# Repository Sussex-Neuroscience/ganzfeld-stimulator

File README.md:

# ganzfeld-stimulator

## Overview
We built a 'full-field' LED stimulator as a visual stimulus generator for in vivo rodent physiology experiments. The stimulator can generate arbitrary temporal patterns of green and UV light (chromatic channels the mouse visual system is sensitive to) such as high frequency flicker or sinusoidal dimming. Stimulation patterns are generated using PWM signals from a microcontroller.

## Parts 

| Item | Link | Quantity | Cost | Datasheet |
|------|------|----------|------|-----------|
| **LEDS**| | | |
| UV LED   |[C3535U- UNL1-A1G11H-380 TSLC, UV LED, 390nm 480mW 125 °, 2-Pin Surface Mount package](https://uk.rs-online.com/web/p/uv-leds/9033769) | (6 x 6 array) = 36 + any spares | £6.88 each | [From RS](https://uk.rs-online.com/web/p/uv-leds/9033769)|
| Green LED | [ams OSRAM3 V Green LED PLCC 2 SMD, TOPLED LT T673-Q1R2-25](https://uk.rs-online.com/web/p/leds/6648197) | (6 x 6 array) = 36 + any spares | £0.196 each| [From RS](https://uk.rs-online.com/web/p/leds/6648197) |
| LED mounting PCB |  [Custom PCB board for mounting LEDs](repo link) | 6 (Each board is populated with 6 of green and 6 UV) | ?? | 
| Soldering stencil | [Custom stencil](repo link) | 1 | ?? |
|**PSU and Drivers**|||
| LED Driver | [Recom LED Driver, 2 → 35V dc Output, 350mA Output, Constant Current Dimmable](https://uk.rs-online.com/web/p/led-drivers/0416913) | ?? | £12.16 each | [detailed](https://g.recomcdn.com/media/Datasheet/pdf/.fYUQjOlW/.t2a80a771bdbb0ef300f7/Datasheet-93/RCD-24.pdf) |
| PSU | [12V dc Output, 5A Output](https://uk.rs-online.com/web/p/ac-dc-adapters/8808408?gb=s) | ?? | £21.38 each |
|**Box Construction**| | |
| Structure | [MakerBeam starter kit](https://www.technobotsonline.com/makerbeamxl-regular-starter-kit-in-black-anodised-threaded.html) | 1 | £102.95 (possible to buy specific parts separately) | [200mm beam technical drawing](https://drive.google.com/drive/folders/0B8h5C_ek_fmKa2E4a2I1NEtXWTQ?resourcekey=0-tFenALGdWDfK6WEzQJMuUQ), [50mm beam technical drawing](https://drive.google.com/drive/folders/1401xnkoKaVmki9BlENUgdnQiJKWathsU) |
| Structure | [MakerBeam Construction Cubes](https://www.technobotsonline.com/makerbeam-xl-black-corner-cubes-pack-of-12.html) | 1x box of 12 (need 8) |  £18.00 for 12 | [corner cube technical drawing](https://drive.google.com/drive/folders/0B8h5C_ek_fmKcEFvbkl0NWtaZ28?resourcekey=0-kpjmWWiNEXZBVXVSDK05Yg) |
| Reflective Walls + floor | [RS PRO Aluminium Metal Sheet 300mm x 500mm, 2mm Thick](https://uk.rs-online.com/web/p/metal-sheets/0434059) | 1*(200x200mm), 4*(50x200mm) | £49.07 for 5 300x500mm sheets |
|**Diffuser** | | |
| Tracing paper | e.g. [amazon](https://www.amazon.co.uk/GLADFRESIT-Translucent-Architecture-Scrapbooking-Printing/dp/B0C3VX6JPX/ref=asc_df_B0C3VX6JPX/?tag=googshopuk-21&linkCode=df0&hvadid=662823090693&hvpos=&hvnetw=g&hvrand=10142952570193465802&hvpone=&hvptwo=&hvqmt=&hvdev=c&hvdvcmdl=&hvlocint=&hvlocphy=1006565&hvtargid=pla-2196737734548&psc=1&mcid=5f2980b322dd33169770b0c6ecff1379) | 2 sheets + spares | £5.99 |
| Diffusion holder | [Custom 3D printed part](repo link) | ?? | ?? |

## Construction

### Building the stimulator structure
We opted to make a 200x200mm box with a ~50mm depth for achieving a uniform intensity of light. The box can easily be scaled larger and smaller to suit your purposes accordingly.

1) Join 4 x 200mm beams to form a square, using the construction cubes in the corners. You need to make 2 of these for the top and bottom of the box.
2) Cut a ~200x200mm piece of aluminium to slot into the centre of one of the square. You'll need to slightly adjust the size so it fits into the grooves of the beams. This will provide the base for the LED PCBs. (drill a hole of diameter xx for wires)
3) Add 4 x 50mm beams upright to the 4 corners of one of the squares.
4) Screw in the other 200x200mm square to these upright beams to form the top of the box.
5) Cut 4 more pieces of aluminium to form the 4 walls of the box. You want them to be flush with the top of the box to maximise reflectivity of the light inside the box.

### Populating the LEDs on the PCB boards
Use the soldering stencil to populate each of the PCB boards with 6 x green and 6 x UV LEDs. The LEDs are arranged in alternating rows of 3 green/UV.

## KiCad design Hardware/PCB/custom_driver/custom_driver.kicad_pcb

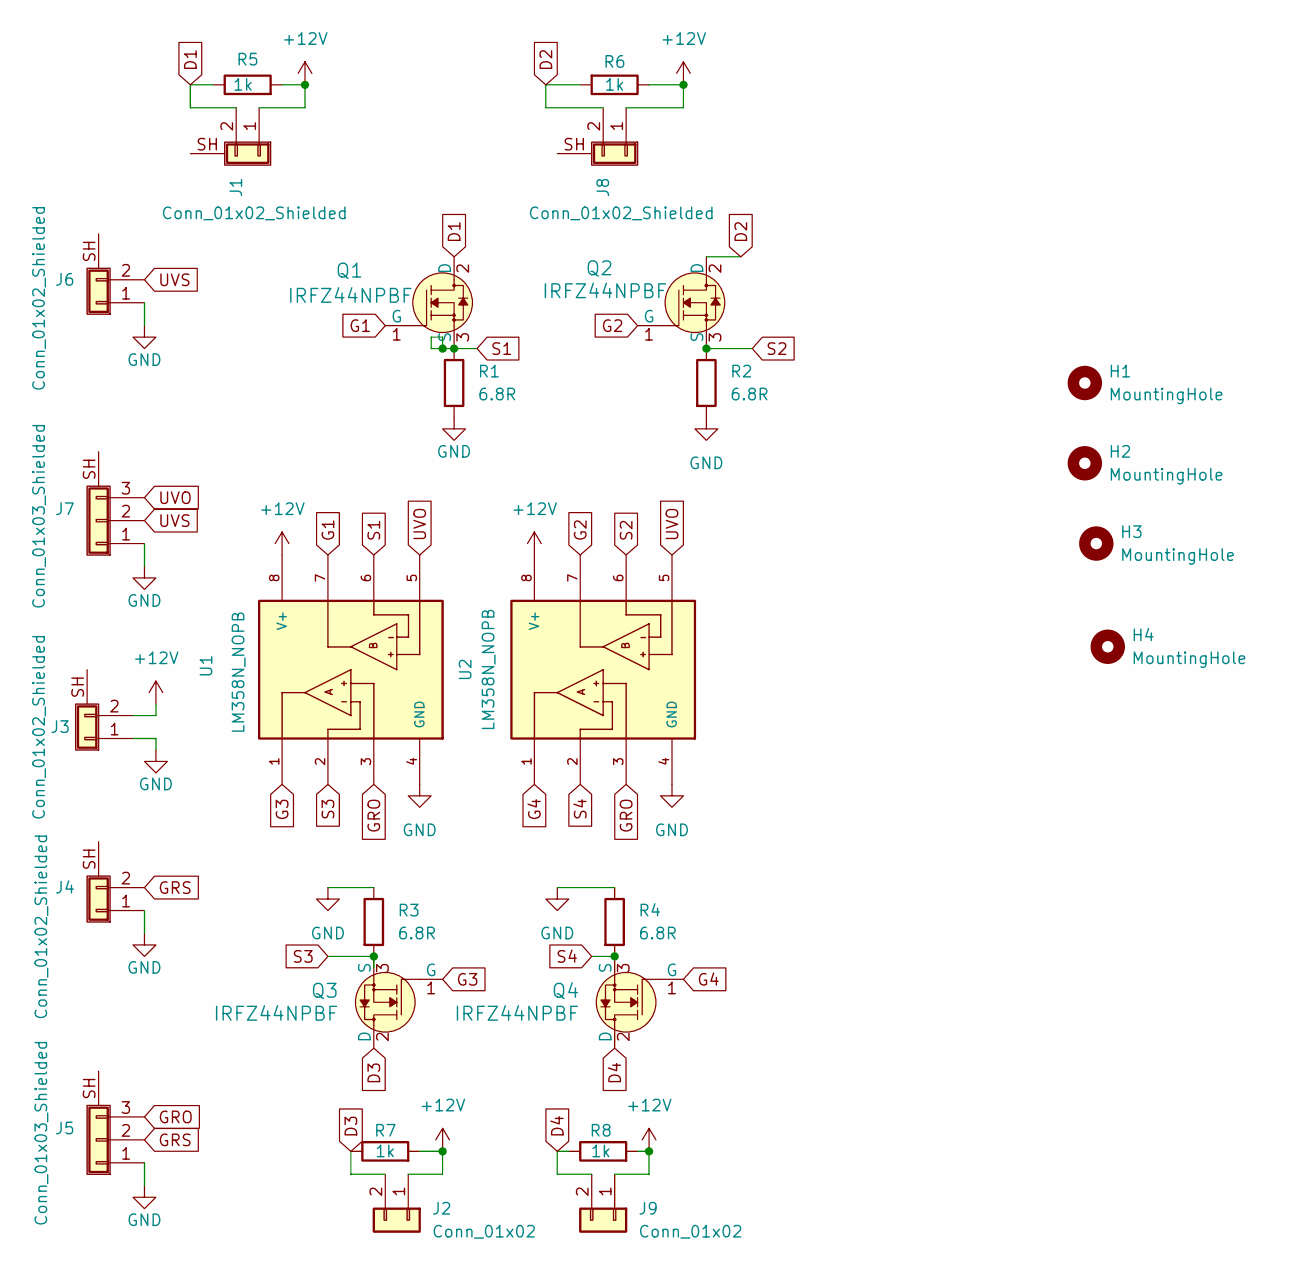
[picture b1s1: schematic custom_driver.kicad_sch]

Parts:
H1, H2, H3, H4: MountingHole; MountingHole_3.2mm_M3
J1, J3, J4, J6, J8: Conn_01x02_Shielded; PinSocket_1x02_P2.54mm_Horizontal
J2, J9: Conn_01x02; PinSocket_1x02_P2.54mm_Horizontal
J5, J7: Conn_01x03_Shielded; PinSocket_1x03_P2.54mm_Horizontal
Q1, Q2, Q3, Q4: IRFZ44NPBF; TO-220-3; MPN IRF510PBF; Digi-Key_PN IRF510PBF-ND
R1, R2: 6.8R; R_Axial_Power_L38.0mm_W6.4mm_P40.64mm
R3, R4: 6.8R; R_Axial_DIN0207_L6.3mm_D2.5mm_P7.62mm_Horizontal
R5, R6, R7, R8: 1k; R_Axial_DIN0207_L6.3mm_D2.5mm_P7.62mm_Horizontal
U1, U2: LM358N_NOPB; LM358N_NOP

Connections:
+12V: J1.1, J2.1, J3.2, J8.1, J9.1, R5.2, R6.1, R7.2, R8.2, U1.8 (V+), U2.8 (V+)
D1: J1.2, Q1.2 (D), R5.1
D2: J8.2, Q2.2 (D), R6.2
D3: J2.2, Q3.2 (D), R7.1
D4: J9.2, Q4.2 (D), R8.1
G1: Q1.1 (G), U1.7
G2: Q2.1 (G), U2.7
G3: Q3.1 (G), U1.1
G4: Q4.1 (G), U2.1
GND: J3.1, J4.1, J5.1, J6.1, J7.1, R1.2, R2.2, R3.1, R4.1, U1.4 (GND), U2.4 (GND)
GRO: J5.3, U1.3, U2.3
GRS: J4.2, J5.2
S1: Q1.3 (S), R1.1, U1.6
S2: Q2.3 (S), R2.1, U2.6
S3: Q3.3 (S), R3.2, U1.2
S4: Q4.3 (S), R4.2, U2.2
UVO: J7.3, U1.5, U2.5
UVS: J6.2, J7.2

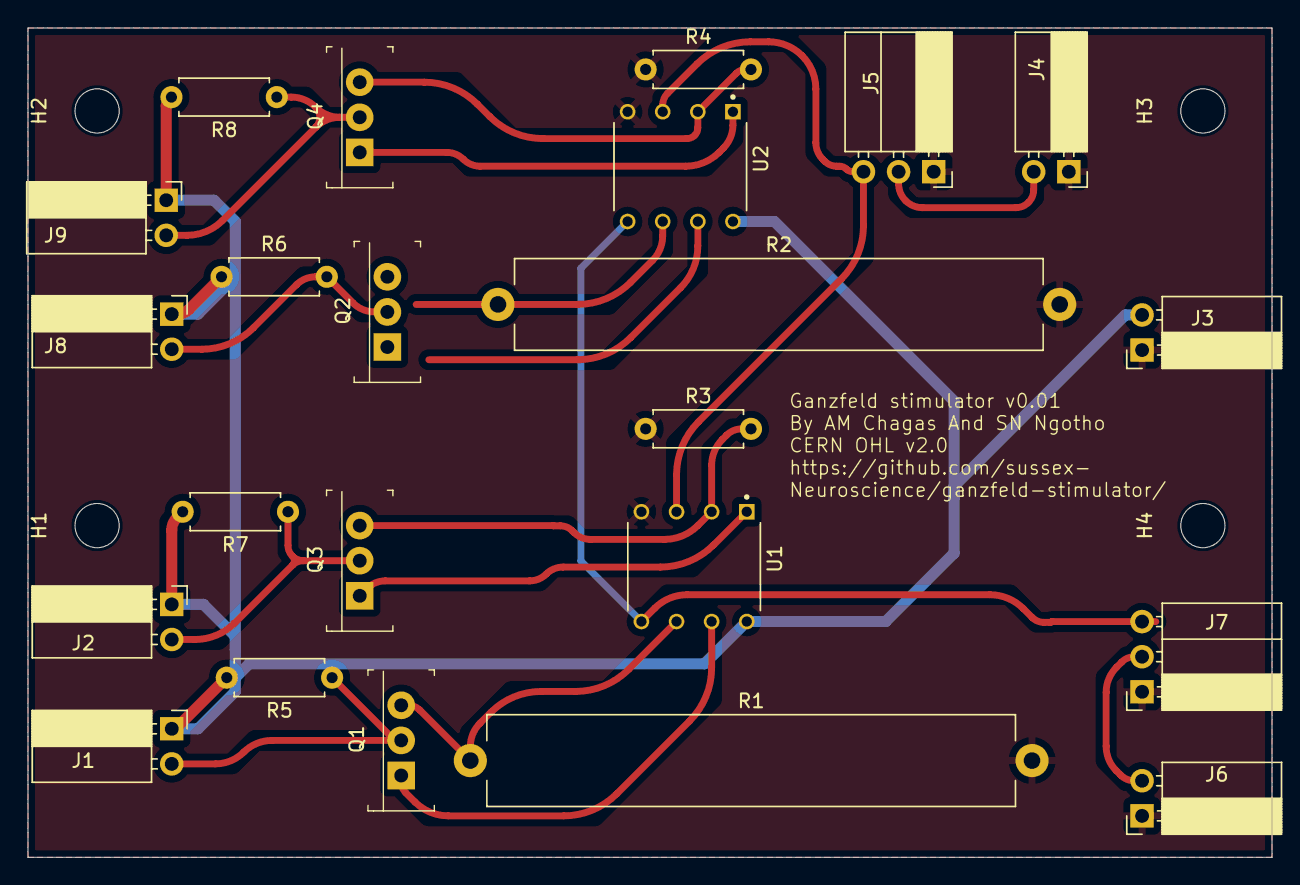
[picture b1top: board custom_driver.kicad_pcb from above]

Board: 2 copper layers, 90.0 x 60.0 mm, 27 parts (0 on the bottom side), 18 nets.

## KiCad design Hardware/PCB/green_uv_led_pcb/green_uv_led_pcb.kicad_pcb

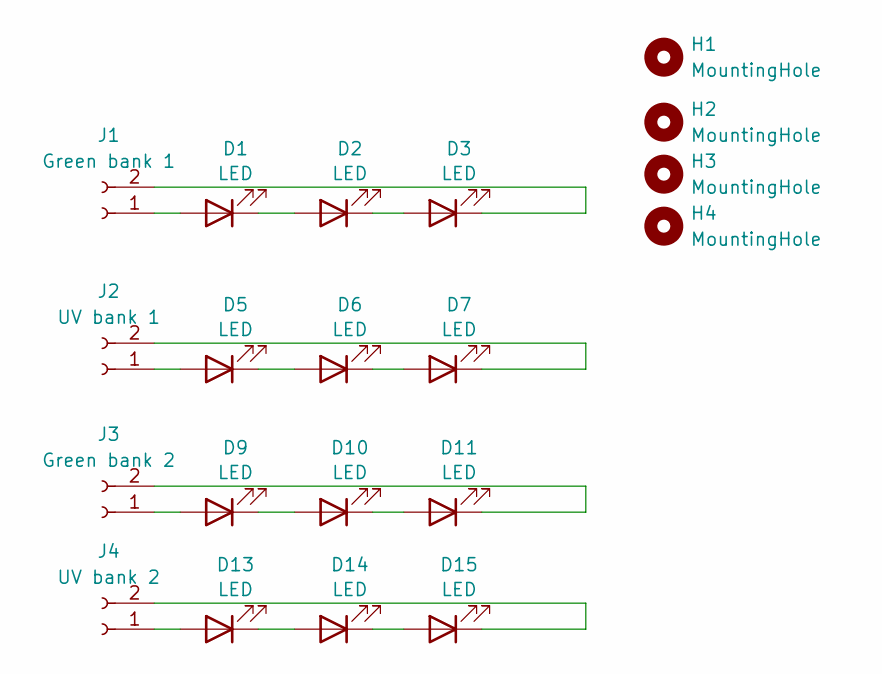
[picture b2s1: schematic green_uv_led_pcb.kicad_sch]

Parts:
D1, D2, D3, D9, D10, D11: LED; LED_PLCC-2_3.4x3.0mm_KA
D5, D6, D7, D13, D14, D15: LED; LED_Cree-XP
H1, H2, H3, H4: MountingHole; MountingHole_3.2mm_M3
J1: Green bank 1; PinSocket_1x02_P2.54mm_Horizontal
J2: UV bank 1; PinSocket_1x02_P2.54mm_Horizontal
J3: Green bank 2; PinSocket_1x02_P2.54mm_Horizontal
J4: UV bank 2; PinSocket_1x02_P2.54mm_Horizontal

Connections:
unnamed: D1.2 (A), J1.1
unnamed: D1.1 (K), D2.2 (A)
unnamed: D2.1 (K), D3.2 (A)
unnamed: D3.1 (K), J1.2
unnamed: D5.2 (A), J2.1
unnamed: D5.1 (K), D6.2 (A)
unnamed: D6.1 (K), D7.2 (A)
unnamed: D7.1 (K), J2.2
unnamed: D9.2 (A), J3.1
unnamed: D9.1 (K), D10.2 (A)
unnamed: D10.1 (K), D11.2 (A)
unnamed: D11.1 (K), J3.2
unnamed: D13.2 (A), J4.1
unnamed: D13.1 (K), D14.2 (A)
unnamed: D14.1 (K), D15.2 (A)
unnamed: D15.1 (K), J4.2

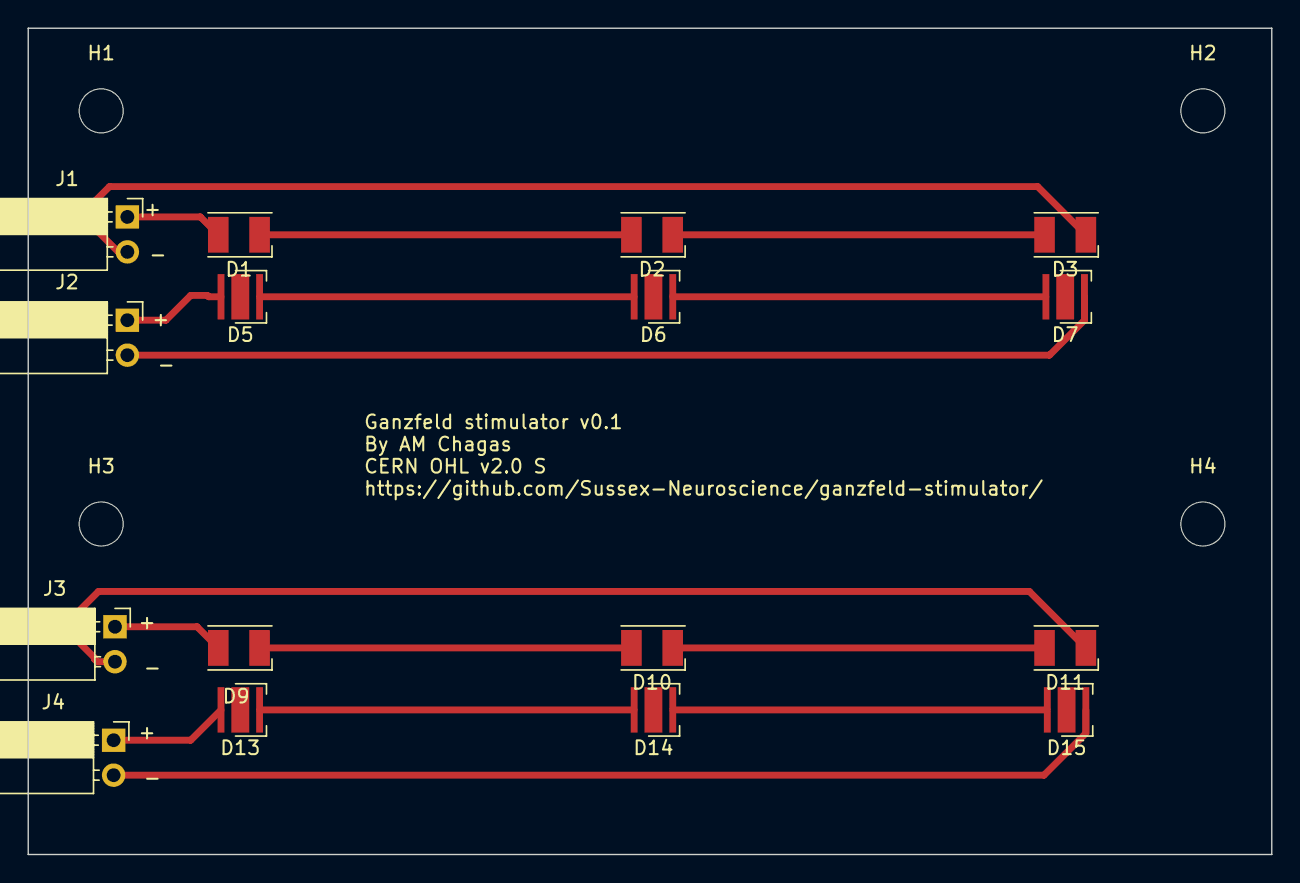
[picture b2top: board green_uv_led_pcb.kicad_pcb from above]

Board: 2 copper layers, 90.3 x 60.0 mm, 20 parts (0 on the bottom side), 16 nets.

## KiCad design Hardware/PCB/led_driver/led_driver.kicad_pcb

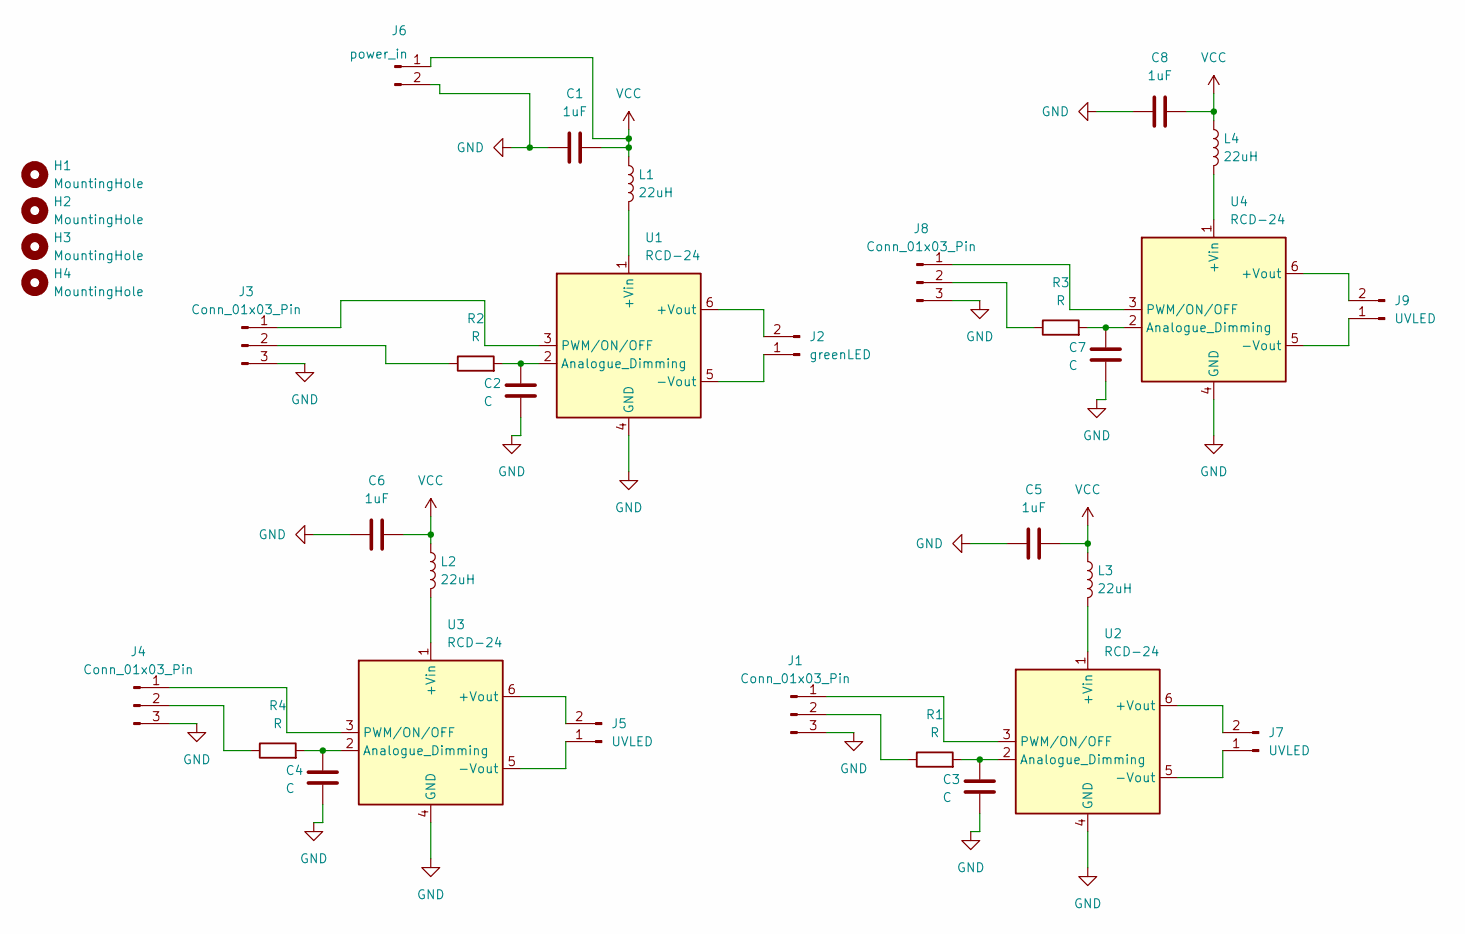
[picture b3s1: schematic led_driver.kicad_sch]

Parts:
C1, C5, C6, C8: 1uF; CP_Radial_Tantal_D4.5mm_P2.50mm
C2, C3, C4, C7: C; CP_Radial_Tantal_D4.5mm_P2.50mm
H1, H2, H3, H4: MountingHole; MountingHole_3.2mm_M3
J1, J3, J4, J8: Conn_01x03_Pin; JST_XH_B3B-XH-A_1x03_P2.50mm_Vertical
J2: greenLED; JST_XH_B2B-XH-A_1x02_P2.50mm_Vertical
J5, J7, J9: UVLED; JST_XH_B2B-XH-A_1x02_P2.50mm_Vertical
J6: power_in; JST_XH_B2B-XH-A_1x02_P2.50mm_Vertical
L1, L2, L3, L4: 22uH; L_Radial_D6.0mm_P4.00mm
R1, R2, R3, R4: R; R_Axial_DIN0411_L9.9mm_D3.6mm_P12.70mm_Horizontal
U1, U2, U3, U4: RCD-24; Converter_DCDC_RECOM_RCD-24_THT

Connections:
GND: C1.1, C2.2, C3.2, C4.2, C5.1, C6.1, C7.2, C8.1, J1.3, J3.3, J4.3, J6.2, J8.3, U1.4 (GND), U2.4 (GND), U3.4 (GND), U4.4 (GND)
unnamed: J1.1, U2.3 (PWM/ON/OFF)
unnamed: J1.2, R1.1
unnamed: J2.1, U1.5 (-Vout)
unnamed: J2.2, U1.6 (+Vout)
unnamed: J3.1, U1.3 (PWM/ON/OFF)
unnamed: J3.2, R2.1
unnamed: J4.1, U3.3 (PWM/ON/OFF)
unnamed: J4.2, R4.1
unnamed: J5.1, U3.5 (-Vout)
unnamed: J5.2, U3.6 (+Vout)
unnamed: J7.1, U2.5 (-Vout)
unnamed: J7.2, U2.6 (+Vout)
unnamed: J8.1, U4.3 (PWM/ON/OFF)
unnamed: J8.2, R3.1
unnamed: J9.1, U4.5 (-Vout)
unnamed: J9.2, U4.6 (+Vout)
unnamed: L1.2, U1.1 (+Vin)
unnamed: C2.1, R2.2, U1.2 (Analogue_Dimming)
unnamed: L3.2, U2.1 (+Vin)
unnamed: C3.1, R1.2, U2.2 (Analogue_Dimming)
unnamed: L2.2, U3.1 (+Vin)
unnamed: C4.1, R4.2, U3.2 (Analogue_Dimming)
unnamed: L4.2, U4.1 (+Vin)
unnamed: C7.1, R3.2, U4.2 (Analogue_Dimming)
VCC: C1.2, C5.2, C6.2, C8.2, J6.1, L1.1, L2.1, L3.1, L4.1

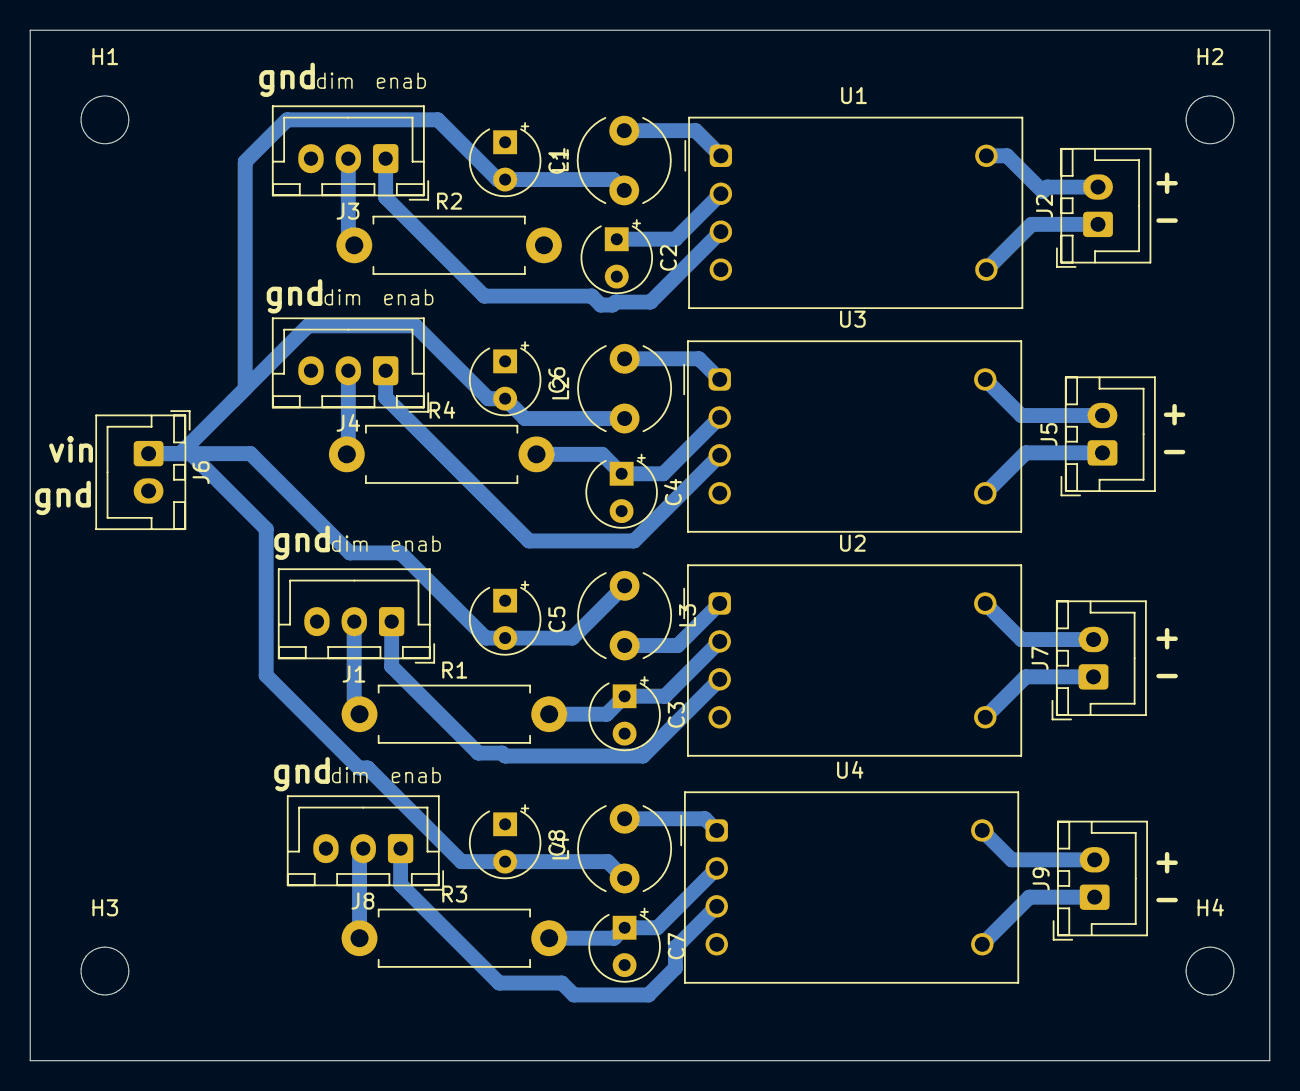
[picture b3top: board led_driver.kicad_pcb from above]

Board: 2 copper layers, 83.0 x 69.0 mm, 33 parts (0 on the bottom side), 26 nets.

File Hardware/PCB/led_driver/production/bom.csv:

Designator,Footprint,Quantity,Value,LCSC Part #
"C1, C5, C6, C8",CP_Radial_Tantal_D4.5mm_P2.50mm,4,1uF,
"C2, C3, C4, C7",CP_Radial_Tantal_D4.5mm_P2.50mm,4,C,
"J1, J3, J4, J8",JST_XH_B3B-XH-A_1x03_P2.50mm_Vertical,4,Conn_01x03_Pin,
J2,JST_XH_B2B-XH-A_1x02_P2.50mm_Vertical,1,greenLED,
"J5, J7, J9",JST_XH_B2B-XH-A_1x02_P2.50mm_Vertical,3,UVLED,
J6,JST_XH_B2B-XH-A_1x02_P2.50mm_Vertical,1,power_in,
"L1, L2, L3, L4",L_Radial_D6.0mm_P4.00mm,4,22uH,
"R1, R2, R3, R4",R_Axial_DIN0411_L9.9mm_D3.6mm_P12.70mm_Horizontal,4,R,
"U1, U2, U3, U4",Converter_DCDC_RECOM_RCD-24_THT,4,RCD-24,

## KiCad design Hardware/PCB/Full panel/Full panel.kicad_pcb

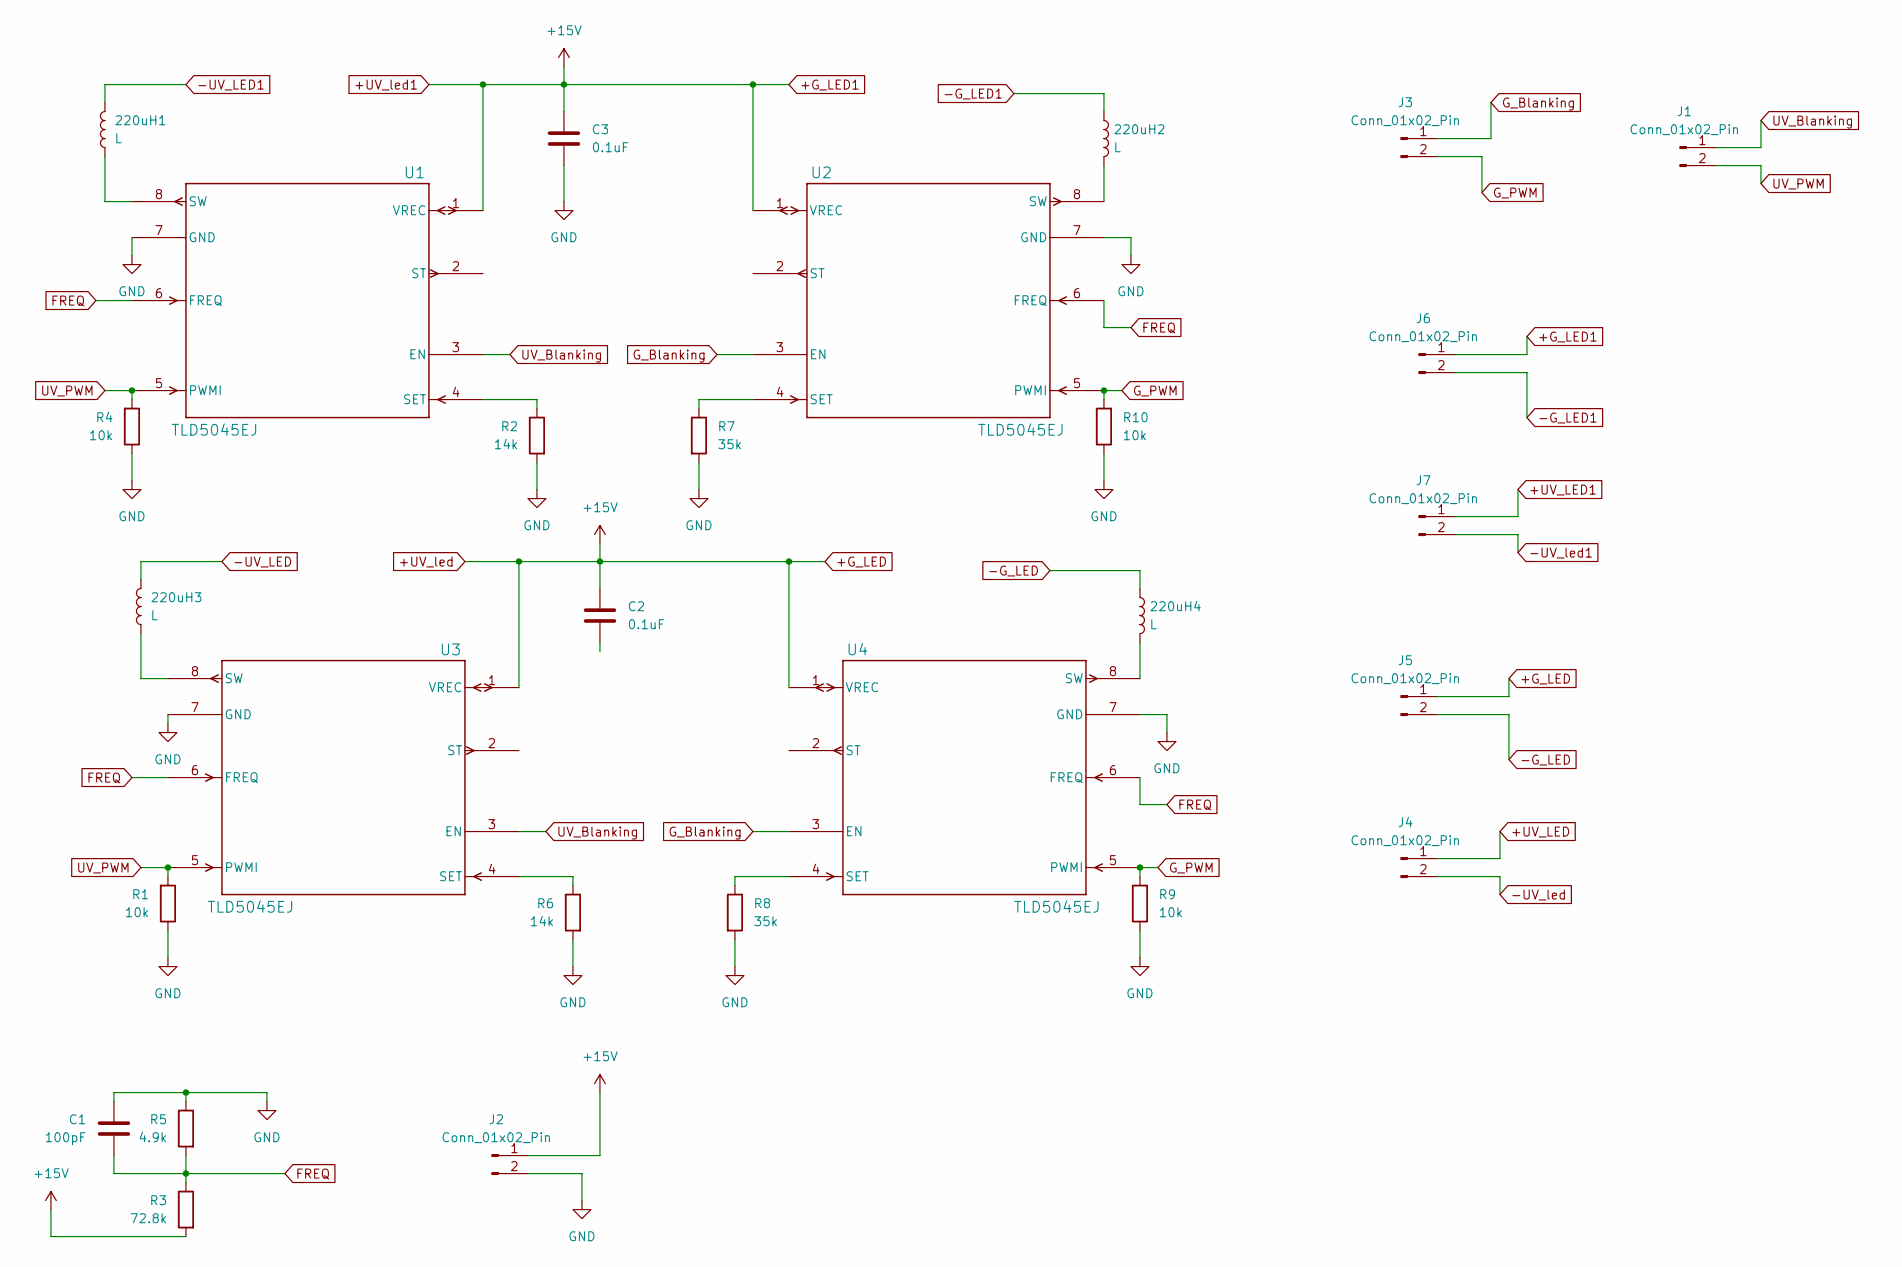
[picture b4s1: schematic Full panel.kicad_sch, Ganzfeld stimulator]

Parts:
220uH1, 220uH2, 220uH3, 220uH4: L; C_0805_2012Metric_Pad1.18x1.45mm_HandSolder
C1: 100pF; C_0805_2012Metric_Pad1.18x1.45mm_HandSolder
C2, C3: 0.1uF; C_0805_2012Metric_Pad1.18x1.45mm_HandSolder
J1, J2, J3, J4, J5, J6, J7: Conn_01x02_Pin; PinSocket_1x02_P2.54mm_Vertical
R1, R4, R9, R10: 10k; C_0805_2012Metric_Pad1.18x1.45mm_HandSolder
R2, R6: 14k; C_0805_2012Metric_Pad1.18x1.45mm_HandSolder
R3: 72.8k; C_0805_2012Metric_Pad1.18x1.45mm_HandSolder
R5: 4.9k; C_0805_2012Metric_Pad1.18x1.45mm_HandSolder
R7, R8: 35k; C_0805_2012Metric_Pad1.18x1.45mm_HandSolder
U1, U2, U3, U4: TLD5045EJ; PG-DSO-8-1_INF

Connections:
+G_LED: C2.1, C3.1, J2.1, J5.1, J6.1, R3.2, U1.1 (VREC), U2.1 (VREC), U3.1 (VREC), U4.1 (VREC)
+UV_LED: J4.1
+UV_LED1: J7.1
-G_LED: 220uH4.1, J5.2
-G_LED1: 220uH2.1, J6.2
-UV_LED: 220uH3.1
-UV_LED1: 220uH1.1
-UV_led: J4.2
-UV_led1: J7.2
FREQ: C1.2, R3.1, R5.2, U1.6 (FREQ), U2.6 (FREQ), U3.6 (FREQ), U4.6 (FREQ)
GND: C1.1, C3.2, J2.2, R1.1, R2.2, R4.1, R5.1, R6.2, R7.2, R8.2, R9.1, R10.1, U1.7 (GND), U2.7 (GND), U3.7 (GND), U4.7 (GND)
G_Blanking: J3.1, U2.3 (EN), U4.3 (EN)
G_PWM: J3.2, R9.2, R10.2, U2.5 (PWMI), U4.5 (PWMI)
unnamed: R2.1, U1.4 (SET)
unnamed: 220uH1.2, U1.8 (SW)
unnamed: R7.1, U2.4 (SET)
unnamed: 220uH2.2, U2.8 (SW)
unnamed: R6.1, U3.4 (SET)
unnamed: 220uH3.2, U3.8 (SW)
unnamed: R8.1, U4.4 (SET)
unnamed: 220uH4.2, U4.8 (SW)
UV_Blanking: J1.1, U1.3 (EN), U3.3 (EN)
UV_PWM: J1.2, R1.2, R4.2, U1.5 (PWMI), U3.5 (PWMI)

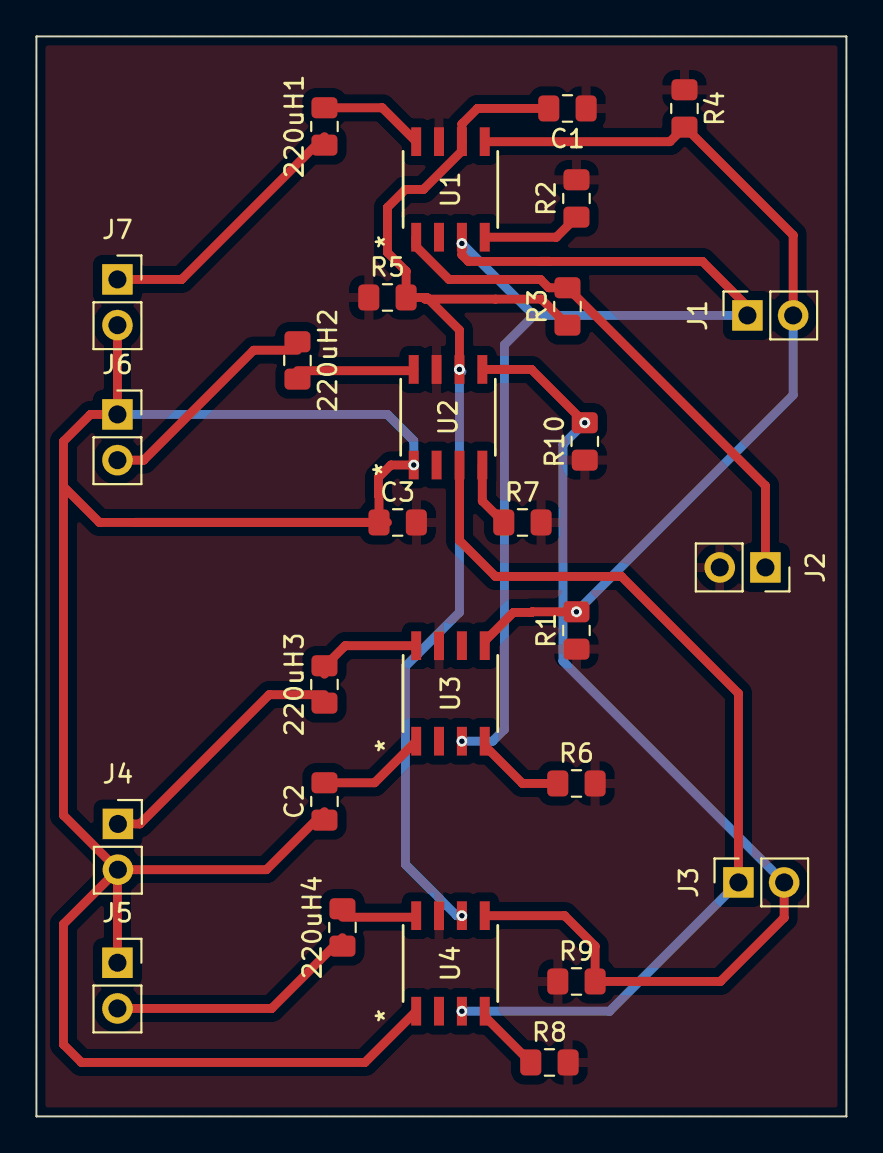
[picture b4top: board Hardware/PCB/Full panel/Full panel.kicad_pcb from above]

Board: 2 copper layers, 45.0 x 60.0 mm, 28 parts (0 on the bottom side), 17 nets.

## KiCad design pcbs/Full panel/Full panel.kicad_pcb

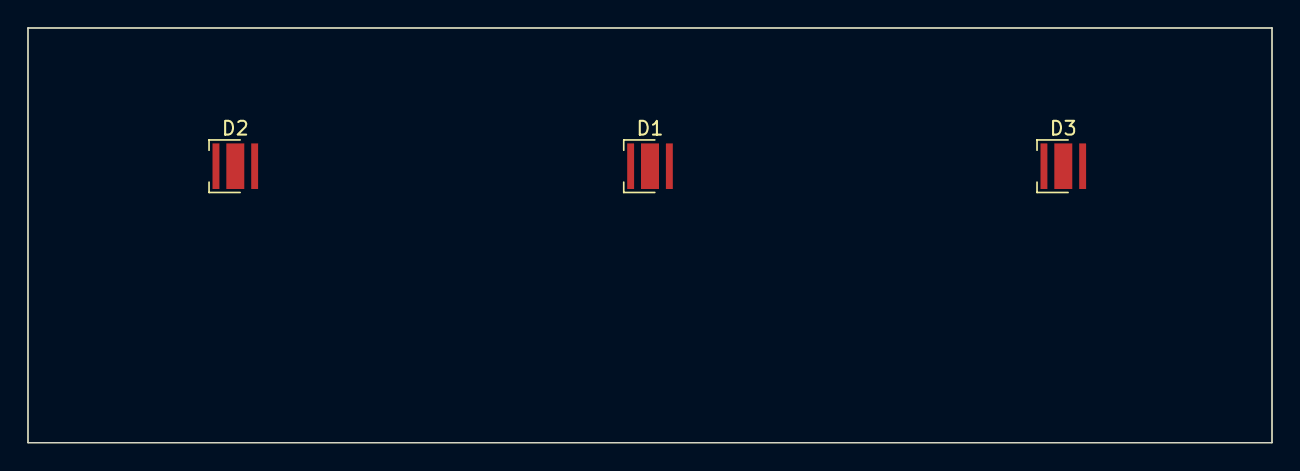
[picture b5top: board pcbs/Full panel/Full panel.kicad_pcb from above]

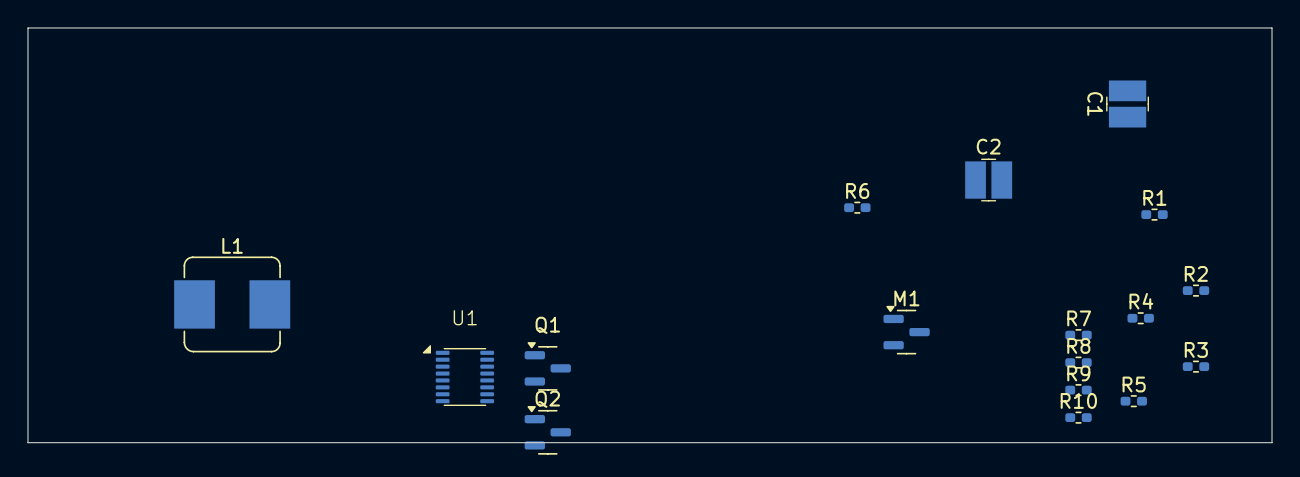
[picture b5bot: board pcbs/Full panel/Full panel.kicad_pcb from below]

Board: 2 copper layers, 90.0 x 30.0 mm, 20 parts (17 on the bottom side), 17 nets, no tracks yet.

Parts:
C1: 4.7uF; SMD-2_3.2x2.5mm
C2: 10uF; SMD-2_3.2x2.5mm
D1, D2, D3: LED; LED_Cree-XP
L1: 47uH; L_Bourns_SRP7028A_7.3x6.6mm
M1: Si2319CDS; SOT-23
Q1: PNP; SOT-23
Q2: NPN; SOT-23
R1: 100k; R_0402_1005Metric_Pad0.72x0.64mm_HandSolder
R2, R8: 1M; R_0402_1005Metric_Pad0.72x0.64mm_HandSolder
R3: 191k; R_0402_1005Metric_Pad0.72x0.64mm_HandSolder
R4: 0.5; R_0402_1005Metric_Pad0.72x0.64mm_HandSolder
R5: 130k; R_0402_1005Metric_Pad0.72x0.64mm_HandSolder
R6: 10k; R_0402_1005Metric_Pad0.72x0.64mm_HandSolder
R7: 14.7k; R_0402_1005Metric_Pad0.72x0.64mm_HandSolder
R9: 1.5k; R_0402_1005Metric_Pad0.72x0.64mm_HandSolder
R10: 1k; R_0402_1005Metric_Pad0.72x0.64mm_HandSolder
U1: LT 3519; ST3519

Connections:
+12V: C1.1, C2.1, R1.2, R2.1, R4.1, R5.1, R8.1, R9.1, U1.5 (Vin), U1.10 (Cathode), U1.11 (ISP)
GND: C1.2, R3.2, R7.2, R10.2
unnamed: D1.2 (A), D2.1 (K)
unnamed: C2.2, D1.1 (K), L1.2, R6.2
unnamed: D2.2 (A), D3.1 (K)
unnamed: D3.2 (A), M1.3 (D)
unnamed: M1.1 (G), Q2.1 (C), R9.2
unnamed: M1.2 (S), R4.2, U1.12 (ISN)
unnamed: Q1.2 (B), R6.1
unnamed: Q1.1 (C), R7.1, U1.13 (FB)
unnamed: Q1.3 (E), R5.2
unnamed: Q2.3 (E), R10.1
unnamed: L1.1, U1.6 (SW), U1.7 (ANODE)
unnamed: R2.2, R3.1, U1.14 (ctrl)
unnamed: R1.1, U1.2 (~OPENLED)
unnamed: R8.2, U1.4 (~SHDN/UVLO)
PWM: Q2.2 (B), U1.3 (PWM)

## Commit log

2023-11-20 create pcb for green leds
2023-11-20 update greenled
2023-11-20 update carvera files
2023-11-20 update green pcb
2023-12-20 new board version
2023-12-20 add gerbers folder
2024-03-07 Update README.md
    Updated parts list + started how to
2024-04-08 preliminary 3d printing and simple arudino PWM stimulation code
2024-04-08 basic sin-flicker convolution
2024-04-09 basic serial -> flicker control
2024-04-11 clean up 3d printing
2024-04-11 Serial controlled stimulus generation update
2024-04-18 move pcbs to dedicated folder and start creating led driver pcb
2024-06-07 update led der
2024-10-25 added full panel pcb
2024-10-25 updated the full panell schematic
2024-10-30 Full Pannel With lt3519 for low voltage application
2024-10-31 full panel with max168
2024-11-27 All work update
2025-01-20 added custom led driver PCB
2025-01-22 upgraded the circuit and the gerber files
2025-02-27 update arduino stimulus generation code
2025-02-28 Create StimulusControlViaSerial_Leonardo_v4.ino
    2 separate pwm channels

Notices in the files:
Hardware/PCB/Full panel/Full panel.kicad_pcb:
CERN OHL V2.05
Hardware/PCB/custom_driver/custom_driver.kicad_pcb:
CERN OHL v2.0
Hardware/PCB/green_uv_led_pcb/green_uv_led_pcb.kicad_pcb:
CERN OHL v2.0 S
